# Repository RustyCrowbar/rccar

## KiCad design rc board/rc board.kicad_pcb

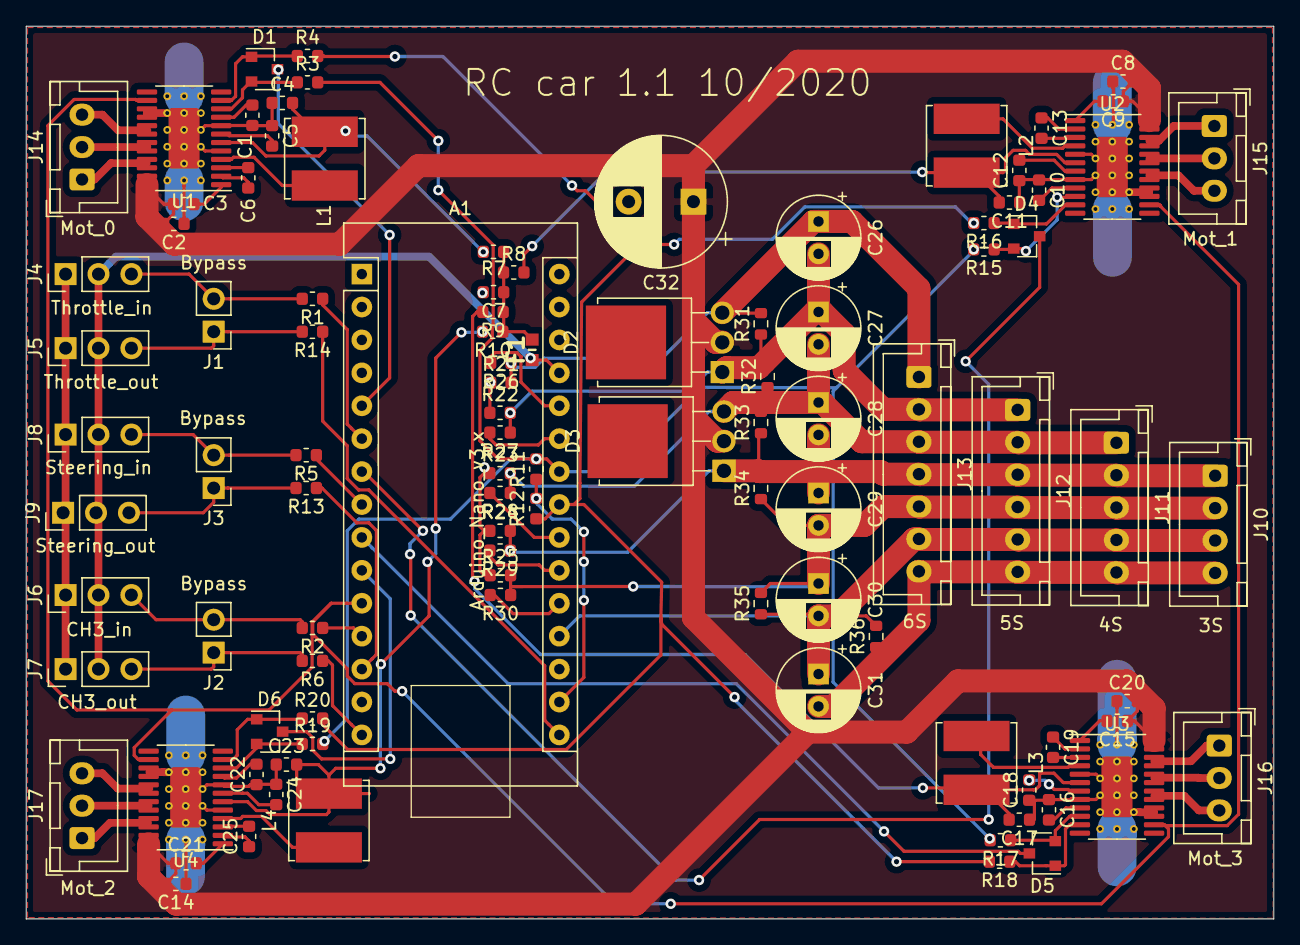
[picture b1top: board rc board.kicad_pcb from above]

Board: 2 copper layers, 96.3 x 68.9 mm, 101 parts (0 on the bottom side), 83 nets.

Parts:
A1: Arduino_Nano_v3.x; Arduino_Nano
C1, C5, C10, C12, C16, C18, C22, C24: 1uF; C_0603_1608Metric
C2, C4, C7, C8, C11, C14, C17, C20, C23: 10uF; C_0603_1608Metric
C3, C9, C15, C21: 100nF; C_0603_1608Metric
C6, C13, C19, C25: 10nF; C_0603_1608Metric
C26, C27, C28, C29, C30, C31: 470uF; CP_Radial_D6.3mm_P2.50mm
C32: 1000uF; CP_Radial_D10.0mm_P5.00mm
D1, D4, D5, D6: BAW56LT3G; SOT-23
D2, D3: MBR2045CTI; TO-251-3-1EP_Horizontal_TabDown
F1: 370mA; FUSC1607X85N
J1, J2, J3: Bypass; PinHeader_1x02_P2.54mm_Vertical
J4: Throttle_in; PinHeader_1x03_P2.54mm_Vertical
J5: Throttle_out; PinHeader_1x03_P2.54mm_Vertical
J6: CH3_in; PinHeader_1x03_P2.54mm_Vertical
J7: CH3_out; PinHeader_1x03_P2.54mm_Vertical
J8: Steering_in; PinHeader_1x03_P2.54mm_Vertical
J9: Steering_out; PinHeader_1x03_P2.54mm_Vertical
J10: 3S; JST_XH_B4B-XH-A_1x04_P2.50mm_Vertical
J11: 4S; JST_XH_B5B-XH-A_1x05_P2.50mm_Vertical
J12: 5S; JST_XH_B6B-XH-A_1x06_P2.50mm_Vertical
J13: 6S; JST_XH_B7B-XH-A_1x07_P2.50mm_Vertical
J14: Mot_0; JST_XH_B3B-XH-A_1x03_P2.50mm_Vertical
J15: Mot_1; JST_XH_B3B-XH-A_1x03_P2.50mm_Vertical
J16: Mot_3; JST_XH_B3B-XH-A_1x03_P2.50mm_Vertical
J17: Mot_2; JST_XH_B3B-XH-A_1x03_P2.50mm_Vertical
L1, L2, L3, L4: 47 uH; L_Bourns_SRN6045TA
R1, R2, R3, R4, R5, R6, R11, R12, R13, R14, R15, R16, R17, R18, R19, R20, R31, R32, R33, R34, R35, R36: 10k; R_0603_1608Metric
R7, R8, R9, R10: 10; R_0603_1608Metric
R21: 100k; R_0603_1608Metric
R22: 150k; R_0603_1608Metric
R23: 180k; R_0603_1608Metric
R24: 330k; R_0603_1608Metric
R25: 470k; R_0603_1608Metric
R26, R27, R28, R29, R30: 560k; R_0603_1608Metric
U1, U2, U3, U4: DRV10983; HTSSOP-24-1EP_4.4x7.8mm_P0.65mm_EP3.4x7.8mm_Mask2.4x4.68mm_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

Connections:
+3V3: A1.17, R11.1, R12.1
+5V: A1.27, F1.1, J4.2, J5.2, J6.2, J7.2, J8.2, J9.2
+5V_0: C4.2, L1.2, R7.2, U1.6
+5V_1: C11.2, L2.2, R8.2, U2.6
+5V_2: C17.2, L3.2, R9.2, U3.6
+5V_3: C23.2, L4.2, R10.2, U4.6
+BATT: C2.2, C3.1, C8.2, C9.1, C14.2, C15.1, C20.2, C21.1, C32.1, D2.2, D3.2, U1.23, U1.24, U2.23, U2.24, U3.23, U3.24, U4.23, U4.24
Batt_0: A1.19, C30.2, C31.1, J10.3, J11.4, J12.5, J13.6, R35.1, R36.2
Batt_1: C29.2, C30.1, J10.2, J11.3, J12.4, J13.5, R25.2, R30.1, R34.1, R35.2
Batt_1_sense: A1.20, R30.2
Batt_2: C28.2, C29.1, D3.1, J10.1, J11.2, J12.3, J13.4, R24.2, R29.1, R33.1, R34.2
Batt_2_sense: A1.21, R29.2
Batt_3: C27.2, C28.1, D3.3, J11.1, J12.2, J13.3, R23.2, R28.1, R32.1, R33.2
Batt_3_sense: A1.22, R28.2
Batt_4: C26.2, C27.1, D2.1, J12.1, J13.2, R22.2, R27.1, R31.1, R32.2
Batt_4_sense: A1.25, R27.2
Batt_5: C26.1, D2.3, J13.1, R21.2, R26.1, R31.2
Batt_5_sense: A1.26, R26.2
CH3_in: J2.1, J7.3, R6.2
CH3_out: J2.2, J6.3, R2.2
DIR: A1.11, U1.14, U2.14, U3.14, U4.14
EN_0: A1.5, D1.3
EN_1: A1.7, D4.3
EN_2: A1.9, D5.3
EN_3: A1.10, D6.3
GND: A1.4, A1.29, C1.1, C2.1, C4.1, C5.1, C7.2, C8.1, C10.1, C11.1, C12.1, C14.1, C16.1, C17.1, C18.1, C20.1, C22.1, C23.1, C24.1, C31.2, C32.2, J4.1, J5.1, J6.1, J7.1, J8.1, J9.1, J10.4, J11.5, J12.6, J13.7, R21.1, R22.1, R23.1, R24.1, R25.1, R36.1, U1.5, U1.8, U1.15, U1.16, U1.25, U2.5, U2.8, U2.15, U2.16, U2.25, U3.5, U3.8, U3.15, U3.16, U3.25, U4.5, U4.8, U4.15, U4.16, U4.25
unnamed: A1.6, R1.1
unnamed: A1.8, R5.1
unnamed: A1.12, R2.1
unnamed: A1.13, R13.1
unnamed: A1.15, R6.1
unnamed: A1.16, R14.1
unnamed: C1.2, U1.9
unnamed: C3.2, U1.1
unnamed: C5.2, U1.7
unnamed: C6.1, U1.2
unnamed: C6.2, U1.3
unnamed: C7.1, F1.2, R7.1, R8.1, R9.1, R10.1
unnamed: C9.2, U2.1
unnamed: C10.2, U2.9
unnamed: C12.2, U2.7
unnamed: C13.1, U2.2
unnamed: C13.2, U2.3
unnamed: C15.2, U3.1
unnamed: C16.2, U3.9
unnamed: C18.2, U3.7
unnamed: C19.1, U3.2
unnamed: C19.2, U3.3
unnamed: C21.2, U4.1
unnamed: C22.2, U4.9
unnamed: C24.2, U4.7
unnamed: C25.1, U4.2
unnamed: C25.2, U4.3
unnamed: D1.1, R4.1, U1.11
unnamed: D1.2, R3.1, U1.10
unnamed: D4.1, R16.1, U2.11
unnamed: D4.2, R15.1, U2.10
unnamed: D5.1, R18.1, U3.11
unnamed: D5.2, R17.1, U3.10
unnamed: D6.1, R20.1, U4.11
unnamed: D6.2, R19.1, U4.10
unnamed: L1.1, U1.4
unnamed: L2.1, U2.4
unnamed: L3.1, U3.4
unnamed: L4.1, U4.4
SCL: A1.24, R3.2, R11.2, R15.2, R17.2, R19.2
SDA: A1.23, R4.2, R12.2, R16.2, R18.2, R20.2
Steering_in: J3.1, J9.3, R13.2
Steering_out: J3.2, J8.3, R5.2
Throttle_in: J1.1, J5.3, R14.2
Throttle_out: J1.2, J4.3, R1.2
U_0: J14.3, U1.17, U1.18
U_1: J15.3, U2.17, U2.18
U_2: J16.3, U3.17, U3.18
U_3: J17.3, U4.17, U4.18
V_0: J14.2, U1.19, U1.20
V_1: J15.2, U2.19, U2.20
V_2: J16.2, U3.19, U3.20
V_3: J17.2, U4.19, U4.20
W_0: J14.1, U1.21, U1.22
W_1: J15.1, U2.21, U2.22
W_2: J16.1, U3.21, U3.22
W_3: J17.1, U4.21, U4.22

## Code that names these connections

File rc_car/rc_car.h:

#pragma once

#include <stdint.h>
//#include <SoftwareSerial.h>

//DRV10987
#include <Wire.h> //I2C Arduino Library
#define ADDR 0x52
#define MAX_FREQ 1000
#define EN_FL_PIN 2
#define EN_FR_PIN 4
#define EN_RL_PIN 6
#define EN_RR_PIN 7
#define DIR D8

#define K 0.00472199
#define MIN_CELL_VOLTAGE 2.8
#define MAX_CELL_VOLTAGE 4.2
#define MAX_BATTERY_CELLS 6
uint8_t cell_pins [MAX_BATTERY_CELLS] =
{
  A0,
  A1,
  A2,
  A3,
  A6,
  A7
};

double cell_const[MAX_BATTERY_CELLS] = 
{
  1.0000,
  2.1915,
  2.6970,
  4.1111,
  4.7333,
  6.6000
};

#define THROTTLE_IN 13
#define THROTTLE_OUT 3
#define STEERING_IN 10
#define STEERING_OUT 5
#define CH3_IN 12
#define CH3_OUT 9

#define FD_RATIO 255
#define RD_RATIO 255

#define OUTPUT_PERIOD 42

struct Differential
{
  uint8_t closedRatio; //255: Both wheels on the axle will turn at the same speed; 0: The differential is fully open.
};

enum dir
{
  FORWARD,
  REVERSE
};

enum d
{
  EN_FL,
  EN_FR,
  EN_RL,
  EN_RR
};

struct battery //All values are in mV
{
  uint16_t cell_0;
  uint16_t cell_1;
  uint16_t cell_2;
  uint16_t cell_3;
  uint16_t cell_4;
  uint16_t cell_5;
};

class Driver
{
public:
  Driver(uint8_t enPin);
  void setCommand(int8_t percent);
  int8_t getCommand();
  int8_t getSpeed();

private:
  uint8_t enPin_;
  uint8_t drv_;//FIXME
  int8_t command_;
};

Driver* drivers[4];
Differential frontDifferential;
Differential rearDifferential;
Differential centerDifferential;

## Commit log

2020-05-09 Starting schematics
2020-05-13 Finiched the driver part, and assigned the IOs to the uC.
2020-05-13 Removed the 3.3V part, powering the uC from 5V.
2020-05-15 Added schottkyes for automatic battery compatibility, and started component layout.
2020-05-15 More routing, added the second driver.
2020-05-15 Added and placed the last 2 drivers, added the battery monitoring part.
2020-05-15 Placed the battery monitoring system.
2020-05-15 Layed down almost all the components but the capacitors.
2020-05-15 Added caps (everybody loves caps), and placed all the components.
2020-05-16 Continued the rooting of MOT3, unlarged the traces.
2020-05-16 Finished routing all the signals, except for some GNDs that probably need filling.
2020-05-16 0 unconnected items!
2020-05-16 Added fill for GND and +Vbatt as well as a text for the project name and date.
2020-05-28 Preparing the code.
2020-05-28 Finished the schematics, generated the gerbers.
2020-06-01 Added the base structures.
2020-06-01 Added high-level functions for inputs ans outputs.
2020-09-20 starting to add the battery volages reading.
2020-10-06 Added functions to display battery info and stop running if it is too low.
2020-10-06 Added bleed resistors in parallel to the caps to allow for a single big cell (bench PSU) to be used.
2020-10-20 Fixed a bug where reseting an error flag on cell voltages.
2020-10-20 Fixed the battery voltage display, and added functions to sample PWM.
